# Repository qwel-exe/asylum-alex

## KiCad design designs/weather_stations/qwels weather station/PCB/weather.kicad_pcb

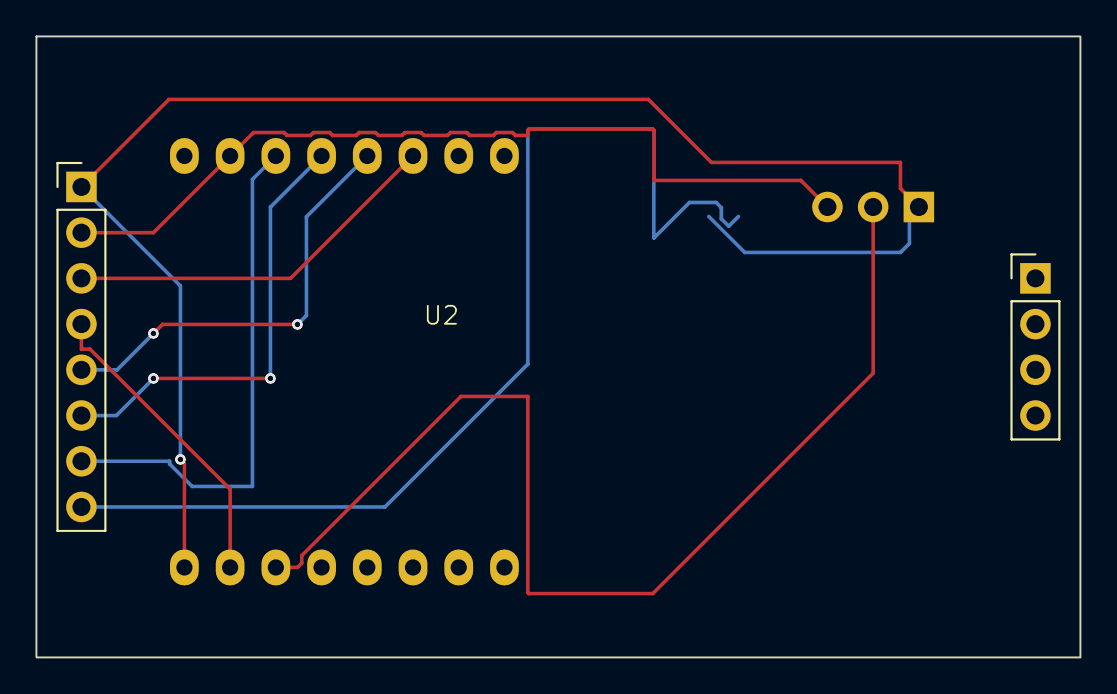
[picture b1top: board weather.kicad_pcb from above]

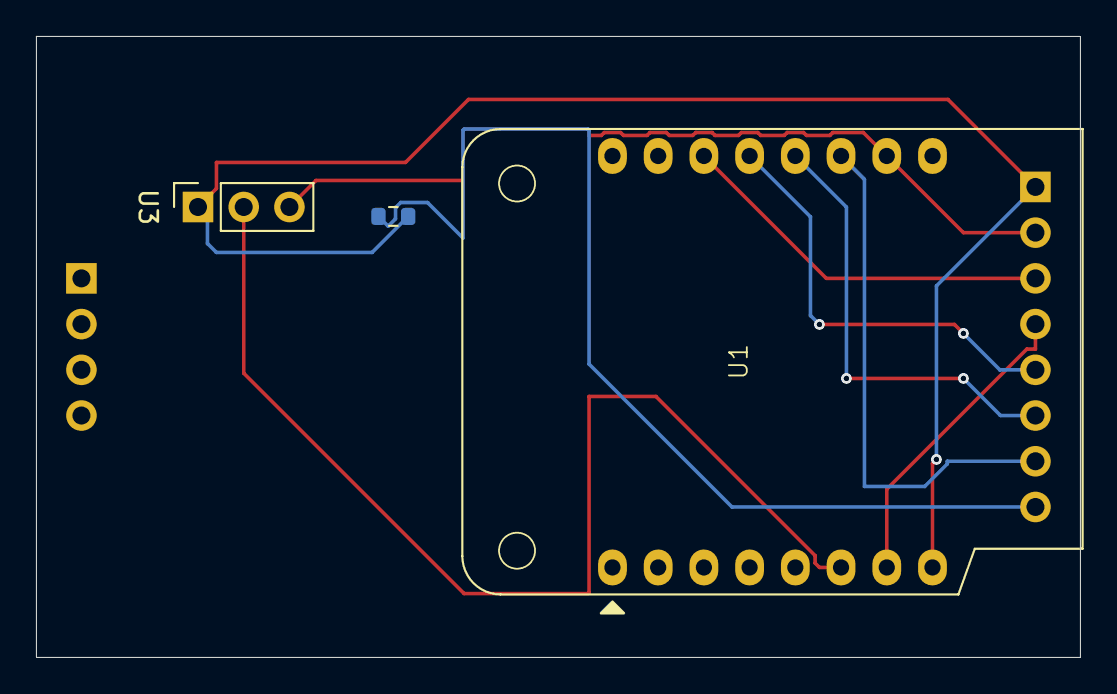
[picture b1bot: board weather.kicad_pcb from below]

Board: 2 copper layers, 58.0 x 34.5 mm, 4 parts (3 on the bottom side), 9 nets.

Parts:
R1: R; R_0603_1608Metric
U1: WEMOS_C3_Mini; WEMOS_C3_mini
U2: TFT_ST7735_SD
U3: AM2302; DHT11

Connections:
3v: R1.1, U1.8 (3V3), U2.1 (3V3), U3.1 (VDD)
unnamed: U1.14 (CS0/IO10), U2.3 (LCD_CS)
unnamed: U1.7 (IO5), U2.4 (EN)
unnamed: U1.13 (IO8), U2.5 (D/C)
unnamed: U1.12 (MOSI/IO7), U2.6 (LCD_MOSI)
unnamed: U1.11 (SCK/IO6), U2.7 (LCD_SCK)
unnamed: R1.2, U2.8 (LED)
SDA: U1.6 (IO4), U3.2 (SDA)
gnd: U1.10 (GND), U2.2 (GND), U3.3 (GND)

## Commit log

2025-01-04 qwel's weather station
